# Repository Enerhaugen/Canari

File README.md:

# Code Documentation:

## main.py

main.py is where most of the functionality is located. It contains the warning logic, microphone code and air quality sensor code, as well as the server code.

### Initializing Server and recieving requests:

In order to initialize the server, we used the Circuitpython HTTPServer library. As The Canari is supposed to work even without WiFi, we have to create a Manual Access Point, which will all<ow the ESP32 to connect to the Raspberry Pi Pico. An example of initializing the server was found in the HTTPServer library documentation, under Manual AP(Access Point): https://docs.circuitpython.org/projects/httpserver/en/stable/starting_methods.html
It important to note that the example uses the server.serve_forever function, which halted the program before the while-loop could be initiated. This was substituted by using the server.poll() function instead inside of the while-loop to continually check for any new requests form the ESP32. To use the server.poll() function, we must also use the server.start function. An example of this was found in the HTTPServer documentation under Tasks between requests: https://docs.circuitpython.org/projects/httpserver/en/stable/examples.html

In order to handle both of the warnings from the ESP32, we created two distinct @server.route's, with two different paths, one for each message the server will recieve. The server route is specified with a path, in our case /message1 and /message 2. They also have the methods "POST". POST is defined as a http method used to send client data to the server. https://developer.mozilla.org/en-US/docs/Web/HTTP/Reference/Methods/POST

This allows us to recieve the messages from the client and handle them accordingly. An example of an implementation of @server.route is provided in the API Documentation under "route". https://docs.circuitpython.org/projects/httpserver/en/latest/api.html

### Warning Functionality

The warning functionality consists of a Piezo Buzzer, an LED Diode, and and OLED Screen. 

The piezo buzzer was configured using a guide: https://learn.adafruit.com/using-piezo-buzzers-with-circuitpython-arduino/circuitpython

The LED functionality was also defined using a guide: https://learn.adafruit.com/circuitpython-digital-inputs-and-outputs/digital-outputs

Both the Buzzer and the LED functionality was placed inside of the warning_on() and warning_off() functionality, that is called whenever a threshold is crossed.

### PMSA003I Air Quality Sensor

The Air quality sensor was configured using this guide: 
https://learn.adafruit.com/pmsa003i/python-circuitpython

The data provided by the pm25.read() function is a key value pair, where the key is a string, and value is an int. This value can therefore be compared to a defined threshold, and whenever the threshold is reached, we can activate the warning functions and display a message on the OLED screen. The guide has already read the pm25.read() data as "aqdata". We can therefore define variables to read specific data from the dictionary:

pm250 = aqdata["pm25 standard"]

This can then be used in comparison with our thresholds. The thresholds were calculated using the time-weighted average for an 8 hour workday. The user will recieve a warning if they are exposed more particulate matter than they can safely breathe in an 8 hour period. The safe value threshold for PM10 exposre is 135. For PM2.5, its 45. 

#### OLED Screen

The OLED will display usefull information and provide context to the warnings. An implementation of the OLED screen was found here: https://docs.circuitpython.org/projects/displayio_ssd1306/en/latest/examples.html

To tailor the code to our purpose, we removed the bitmap and set the height to HEIGH // 5, to fit two rows of text on the screen. The functionality that activates the screen and displays text was placed inside of the warning_oled_text(message) function, in order to reduce redundant code as it will be used frequently. Oled_reset was set to none, and the busio and board libraries was used to set I2C to the correct pins. This solution was inspired by the setup-code from the PMSA003I, where busio was used in a similiar manner to use the correct pins. An example of such an implementation of busio was found here under Circuitpython and python usage: https://learn.adafruit.com/pmsa003i/python-circuitpython

The display.sleep() and display.wake() functions are used to sleep the OLED screen when no warnings are active, and wake the screen when a warning has been sent. Both functions were found here: https://docs.circuitpython.org/projects/displayio_ssd1306/en/latest/api.html

To avoid layering text on the OLED, we used splash.pop() in order to remove the text from the OLED screen. the pop() functionality was found in displayio's documentation, under displayio.Group():

https://docs.circuitpython.org/en/latest/shared-bindings/displayio/

Its important to note that both the PMSA003I and the OLED screen share the same pins - GP0 and GP1. When we tried to use different pins for the components, we recieved an error - ValueError: I2C peripheral in use

A potential solution was found on raspberrypi's forum: https://forums.raspberrypi.com/viewtopic.php?t=328834#p1968307

By connecting both components to the same pins and ensuring that they have different I2C adresses and initializing the i2c bus once, the issue was solved. We kept the example I2C adress provided by the OLED coding example (0x3). The PMSA003I already has a predefined adress (0x12), as seen here under Usage: https://learn.adafruit.com/pmsa003i/wippersnapper-setup

### MAX4466 Mic Amp

To read accurate values from the MAX4466 microphone, we took inspiration from the following guide:

https://lastminuteengineers.com/max4466-arduino-tutorial/

The guide details how we can read peak-to-peak values from the microphone to achieve accurate readings. The difference between the implementation found in the guide and our program, is that we use an array to gather 50 samples instead of any time functions.  When the array has 50 samples, we define two variables - min_sample and max_sample. min_sample is set to the lowest value found in the array, and max_samples is set to the highest. 

To find the peak-to-peak value, we subtract min_sample from max_sample. This becomes our peak-to-peak value. We can use this value to define decibels, by utilizing a sound source and a sound meter. By utilizing this technique, we found that a peak-to-peak value of roughly 20 000 corresponds to about 85 decibels, which can damage hearing over an 8 hour workday. A peak to peak value of roughly 65 000 corresponds to about 95 decibels. If the peak-to-peak value exceeds either of these values, the warning functions will be called, and the user will recieve relevant information on the OLED display.

### Warnings and Warning Cooldowns
When a threshold is crossed, a warning will be sent to the user. To avoid annoying the user, they will only recieve a limited amount of warnings. The user will therefore only recieve a warning if they have recieved fewer warnings then three. If they have recieved three warnings, we must assume that they have taken preemptive measures to avoid injury. This was done by defining a variable as 0 for each specific warning, and increasing it by 1 every time the relevant warning has been sent. If the user has recieved over 3 warnings, the warning functionality will not be called, nor the cooldowns reset.

There must be a time interval between the users warnings, in order to avoid spamming them. To achieve this, we define variables such as warning_daily_cooldown before the loop is initiated. When a warning is sent, warning_daily_cooldown will be set to 3000. As the variable will be subracted by 1 every iteration of the loop, and the loop runs once every 0.1 second, this will result in a cooldown of 5 minutes before a warning can be sent again. In cases where the health of the user is in immidiate danger, such as when they are exposed to over 95 decibels, the cooldown is slightly shorter, at 2 minutes.

We used the Circuitpython Time library in order to run the loop once every 0.1 seconds using the time.sleep() function. This function sleeps the program for a set amount of time by defining time.sleep as 0.1 as such:

time.sleep(0.1)

This allows us to set timers and halt the program whenever needed, such as after every time warning_on() is called. This functionality was found in the time library documentation:

https://docs.circuitpython.org/en/latest/shared-bindings/time/

## code.py

code.py is used in the ESP32. It contains the connection logic to handle the connection to the Raspberry Pi Pico, as well as the vibration sensor logic.

When the warning() function is called, the LED and Piezo Buzzer will all activate for 5 seconds, before turning off. To halt the program for a period of time, we used the time library, which gives us access to time related functionality. In this case, time.sleep was utilized, which slept the program for 5 seconds before resuming and turning off the warnings. The function is used whenever the threshold for sound or air is reached, or when the server recieves a post request from the client.

### Connecting the ESP32 to the Raspberry Pi Pico Access Point and sending post requests:

In order to connect to the access point created on the Pi Pico, the documentation specifies that we must use the wifi.radio.connect, and specify the networks SSID and its password. Found under class wifi.Radio - Connect in the documentation: 

https://docs.circuitpython.org/en/10.0.3/shared-bindings/wifi/index.html 

The connection logic was placed in a while-loop and a try-except block, to ensure that the program will continously try to connect to the access point if the initial attempt fails. When connection has been established, the while loop will break. 

To send the data to the server, we utilzed the adafruit_requests.Session class, with the post function to send a HTTP post request to the server. After the post request is sent, we use the .close() function in order to free the socket. The URL in the post requests was specified to reach the relevant server routes. Documentation was found here, under adafruit_requests.Response, and adafruit_requests.Session:

https://docs.circuitpython.org/projects/requests/en/latest/api.html#implementation-notes

An example of implementation was found here: 
https://docs.circuitpython.org/projects/requests/en/2.0.5/examples.html

### Vibration sensor logic

The vibration sensor is incapable of sensing the intensity and strength of a vibration, and can only return a boolean. We must therefore use a baseline and calculate how long the vibration sensor needs to vibrate before we must send a warning to the user. The baseline was chosen by selecting a handheld tool that exposes the user to strong vibrations. The tool selected excerted a vibration strength of 20 m/s², which we used to calculate the baseline.

We calculated this baseline to be 7,5 minutes before preventative measures must be taken, and 30 minutes before the daily threshold has been reached. Since we use time.sleep as our timing mechanism, we must calculate this threshold to seconds. We therefore end up with 450 seconds before the preventative warning is sent, and 1800 seconds before the daily threshold is reached. To account for potential false negatives and time spent sending the post request, we reduced this to 420 seconds and 1680 seconds respectively.

The vibration sensor itself returns either True or False using the digitalio.DigitalInOut - value function. If the sensor detects vibration, this value returns a True. Otherwise, it returns a False.  If the sensor returns a True value, the vibration count will start ticking upwards, incrementing with 1 per second the vibration is active. When the counts reach the threshold, a post request will be sent to the relevant server route ("/message1" for preventative measures,  "/message2" for daily threshold) and handled accordingly by the Raspberry Pi Pico. The user will then recieve a warning in the central unit with a warning to either take preventative measures, or completely stop the task which is causing them to vibrate, depending on the threshold that has been reached.

In case the post request failed, we placed it in a try-exception block to retry sending the request.

The vibration sensor itself was implemented using the circuitpython libraries board and digitalio. The board library is used with the digitalio library, and allows us to specify the pins used by the sensor. An example of implementation was found here: 

https://learn.adafruit.com/circuitpython-libraries-on-any-computer-with-raspberry-pi-pico/gpio

# Er dette nok referering? hør med fahad

Referanser 3D modeler deler:
ESP32-S3
https://grabcad.com/library/seeed-studio-xiao-esp32s3-1

MAX4466
https://grabcad.com/library/adafruit-max4466-module-1

Arduino Pico: 
https://grabcad.com/library/mbus-master-master-shield-for-arduino-mkr-1 

SW-420:
https://grabcad.com/library/sw-420-1

PMSAA003I:
https://github.com/adafruit/Adafruit_CAD_Parts/tree/main/4632%20PMSA003I

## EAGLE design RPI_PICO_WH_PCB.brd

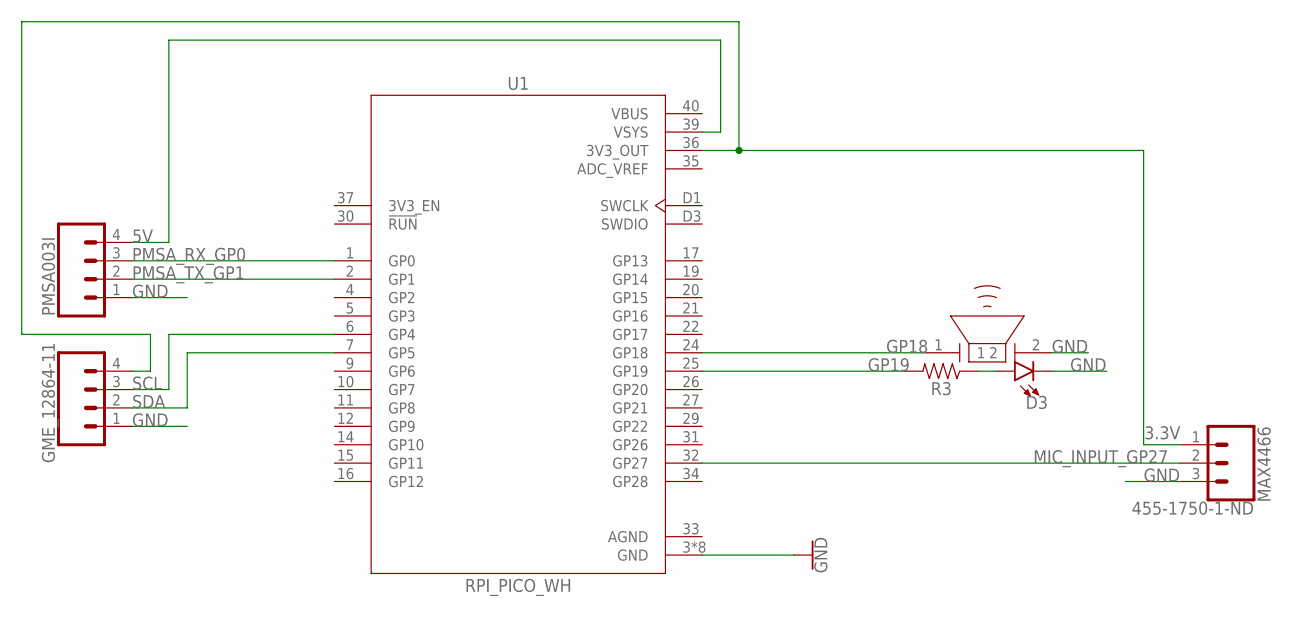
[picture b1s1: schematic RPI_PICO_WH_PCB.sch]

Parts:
D3: LED5MM; LED_5MM
GME_12864-11: CONN_04PTH; 1X04
LS1: PIEZO
MAX4466: 455-1750-1-ND; 1X03
PMSA003I: CONN_04PTH; 1X04
R3: AXIAL-0.3
U1: RPI_PICO_WH; PI_PICO_WH

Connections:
3.3V: GME_12864-11.4, MAX4466.1, U1.36 (3V3_OUT)
5V: PMSA003I.4, U1.39 (VSYS)
ADC_VREF: U1.35 (ADC_VREF)
AGND: U1.33 (AGND)
GND: D3.K (C), GME_12864-11.1, LS1.2, MAX4466.3, PMSA003I.1, U1.3 (GND), U1.8 (GND), U1.13 (GND), U1.18 (GND), U1.23 (GND), U1.28 (GND), U1.38 (GND), U1.D2 (GND)
GP18: LS1.1, U1.24 (GP18)
GP19: R3.P$2 (2), U1.25 (GP19)
MIC_INPUT_GP27: MAX4466.2, U1.32 (GP27)
unnamed: D3.A, R3.P$1 (1)
PMSA_RX_GP0: PMSA003I.3, U1.1 (GP0)
PMSA_TX_GP1: PMSA003I.2, U1.2 (GP1)
SCL: GME_12864-11.3, U1.6 (GP4)
SDA: GME_12864-11.2, U1.7 (GP5)
VBUS: U1.40 (VBUS)

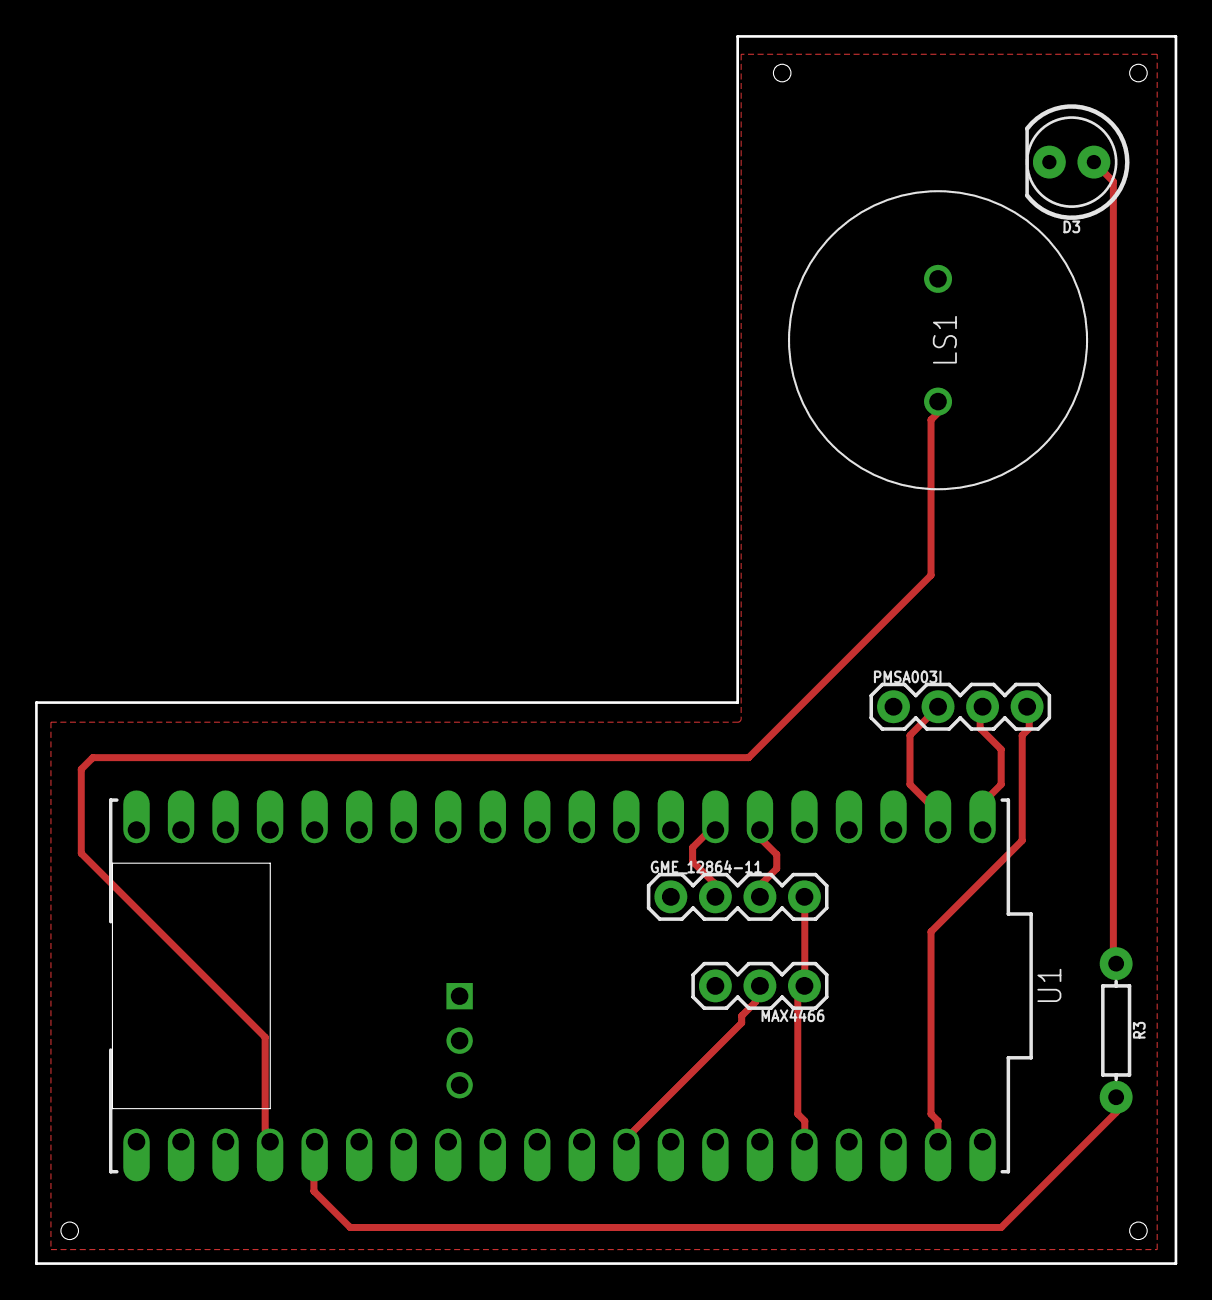
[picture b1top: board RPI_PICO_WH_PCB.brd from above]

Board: 2 copper layers, 65.0 x 70.0 mm, 7 parts (0 on the bottom side), 11 nets.

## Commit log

2026-04-09 Create main.py
    Initital Main File, with microphone, AQ sensor, and vibration sensor.
2026-04-25 Update main.py
    Re-worked main, added server, tweaked functionality, removed LCD code
2026-04-25 Create server.py
    Created a server for the raspberry pi pico through an Access Point, using circuitpython
2026-04-25 Update README.md
    Added documentation of server initialization
2026-04-26 Create code.py
    Uploaded ESP32 code, with connection logic and vibration sensor logic
2026-04-26 Update README.md
    Added Headers
2026-04-26 Update main.py
    added immidiate warning
2026-04-26 Update main.py
    added cooldown functionality to PMSA003I AQ Sensor, as to not spam user with warnings
2026-04-27 Update main.py
    adjusted sound thresholds
2026-04-27 Update main.py
    updated cooldown variables to be 5 minutes
2026-04-29 Update main.py
    Added OLED Code
2026-04-29 Add references for 3D model parts
    Added references for various 3D model parts including ESP32-S3, MAX4466, Arduino Pico, SW-420, and PMSAA003I.
2026-04-30 Update main.py
    fixed pmsa003i deathloop
2026-04-30 Update main.py
    added countdown for pmsa warnings
2026-04-30 Update main.py
    corrected GP pin for led light
2026-05-03 Update main.py
    added connection server route
2026-05-03 Rename Vibration_ESP32.f3d to 3d_models/Vibration_ESP32.f3d
2026-05-03 Rename code.py to ESP32/code.py
2026-05-03 Rename main.py to Raspberry_Pi_Pico/main.py

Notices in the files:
parts and their libraries:
SparkFun-LED: Licensing: Creative Commons ShareAlike 4.0 International - https://creativecommons.org/licenses/by-sa/4.0
